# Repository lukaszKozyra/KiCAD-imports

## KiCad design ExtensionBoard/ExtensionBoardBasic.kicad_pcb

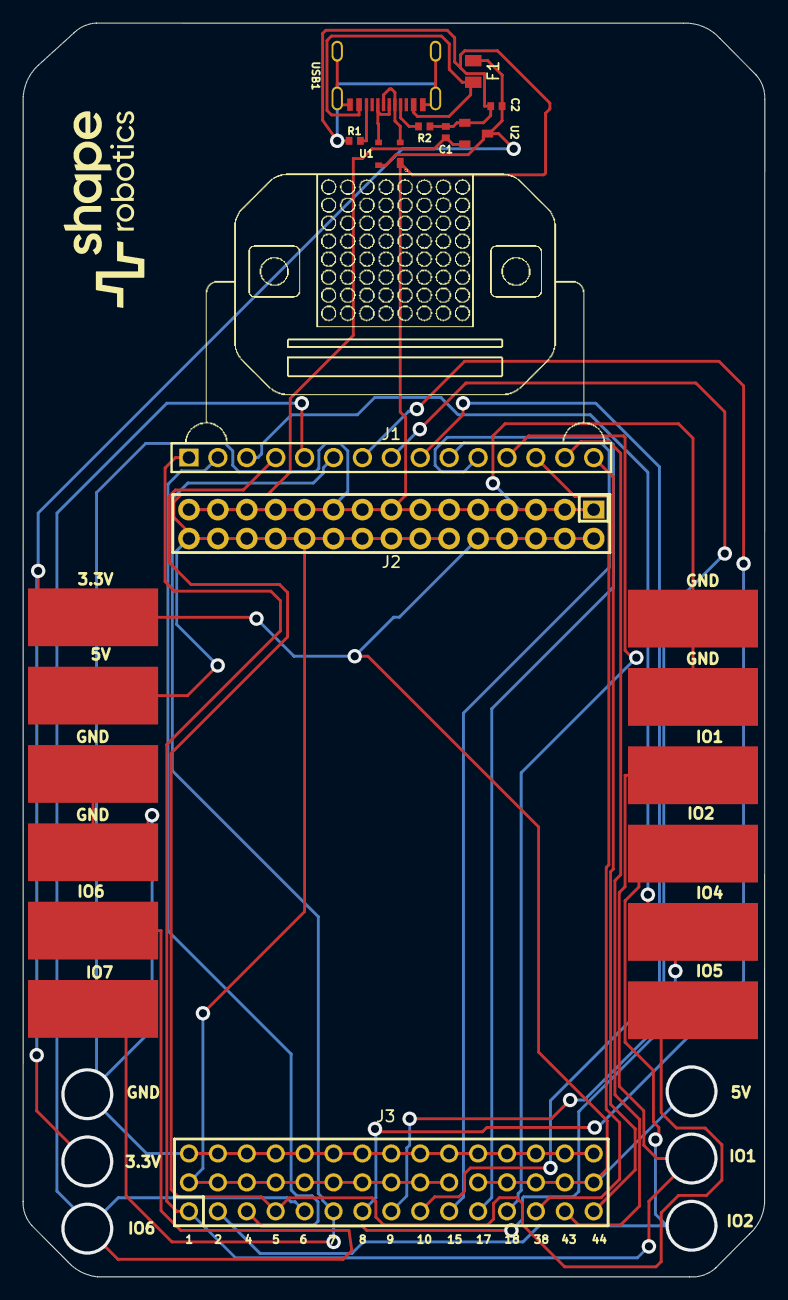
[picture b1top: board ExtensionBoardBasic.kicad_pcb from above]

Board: 4 copper layers, 65.2 x 110.2 mm, 11 parts (0 on the bottom side), 23 nets.

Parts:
C1, C2: 1uF; 0402C
F1: JSMD0805-110; 0805
J1: KH-2.54FH-1X15P-H8.5; HDR-TH_15P-P2.54-V-F
J2: PM2.54-2*15; HDR-TH_30P-P2.54-V-F-R2-C15-S2.54
J3: KH-2.54PH180-3X15P-L11.5; HDR-TH_15P-P2.54-V-M-R3-C15-S2.54
R1, R2: 5.1k; 0402R
U1: Unidirectional 5.5V 6V SOT-143 Diodes - ESD RoHS; SOT143B
U2: C193852; SOT-23
USB1: C167321

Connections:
+3.3: C1.2, J2.12, J2.14, J2.16, J2.18, J2.20, J2.22, J2.24, J2.26, J2.28, J2.30, J3.16, J3.17, J3.18, J3.19, J3.20, J3.21, J3.22, J3.23, J3.24, J3.25, U2.2 (VOUT)
+5: C2.2, F1.1, J2.2, J2.4, J2.6, J2.8, J2.10, J3.26, J3.27, J3.28, J3.29, J3.30, U1.4 (Vcc), U2.3 (VIN)
//IO01: J1.1, J3.1
//IO02: J1.2, J3.2
//IO4: J1.3, J3.3
//IO5: J1.4, J3.4
//IO6: J1.5, J3.5
//IO7: J1.6, J3.6
//IO8: J1.7, J3.7
//IO9: J1.8, J3.8
//IO10: J1.9, J3.9
//IO15: J1.10, J3.10
//IO17: J1.11, J3.11
//IO18: J1.12, J3.12
//IO38: J1.13, J3.13
//IO43: J1.14, J3.14
//IO44: J1.15, J3.15
//fuse: F1.2, USB1.A4B9 (VBUS), USB1.B4A9 (VBUS)
D_N: U1.2 (I/O_1), USB1.A7 (DN1), USB1.B7 (DN2)
D_P: U1.3 (I/O_2), USB1.A6 (DP1), USB1.B6 (DP2)
GND: C1.1, C2.1, J2.1, J2.3, J2.5, J2.7, J2.9, J2.11, J2.13, J2.15, J2.17, J2.19, J2.21, J2.23, J2.25, J2.27, J2.29, J3.31, J3.32, J3.33, J3.34, J3.35, J3.36, J3.37, J3.38, J3.39, J3.40, J3.41, J3.42, J3.43, J3.44, J3.45, R1.1, R2.1, U1.1 (GND), U2.1 (VSS), USB1.A1B12 (GND), USB1.B1A12 (GND)
unnamed: R2.2, USB1.A5 (CC1)
unnamed: R1.2, USB1.B5 (CC2)

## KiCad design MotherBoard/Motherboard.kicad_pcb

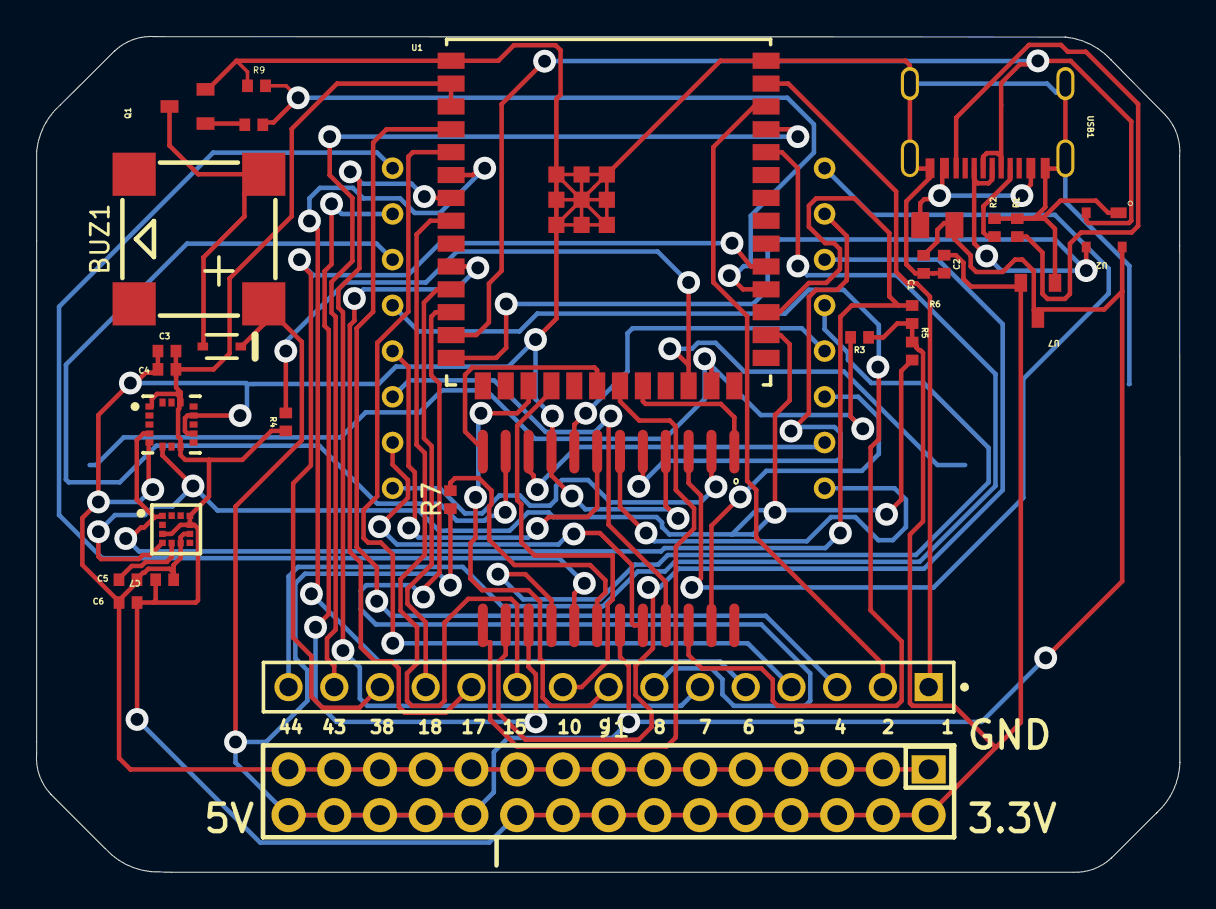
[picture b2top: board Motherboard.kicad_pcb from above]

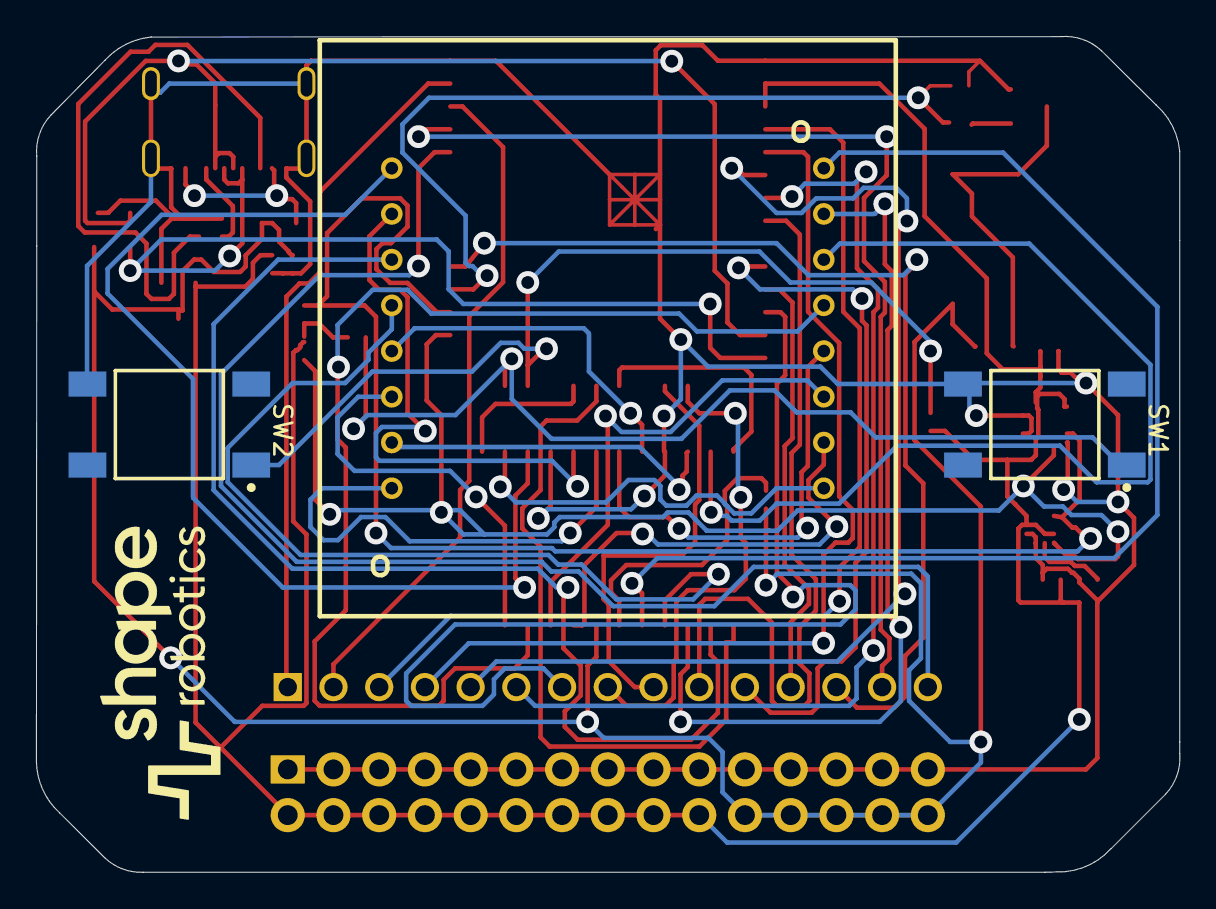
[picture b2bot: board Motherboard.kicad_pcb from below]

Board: 4 copper layers, 63.5 x 46.4 mm, 32 parts (3 on the bottom side), 51 nets.

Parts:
BUZ1: 2.7kHz; BUZ-SMD_4P-L8.5-W8.5-P8.50-BR
C1, C2: 1uF; 0402C
C3: 10pF; 0402C
C4, C5, C6: 100nF; 0402C
C7: 10uF; 0402C
D1: 1N4148WS-7-F; DIOD-SOD323-2-A_V
F1: JSMD0805-110; 0805
J1: 22-28-4157; FP-22-28-4157-MFG
J2: X6521WV-2x15H-C60D30; HDR-TH_30P-P2.54-V-F-R2-C15-S2.54
L1: SZ421288N/64; LED-SEG-TH_SZ421288N-64
Q1: NCE2302; SOT-23
R1, R2: 5.1k; 0402R
R3, R4, R5, R6, R7, R9: 10K; 0402R
R8: 470; 0402R
SW1, SW2: FSM4JSMATR; TECO-FSM4JSMATR_V
U1: ESP32 S3; ESP32 S3 WROOM 1
U2: Unidirectional 5.5V 6V SOT-143 Diodes - ESD RoHS; SOT143B
U4: LIS2MDLTR; FP-LGA-12-DM00170568-MFG
U5: LIS3DHTR; FP-LGA-16-7983231-MFG
U6: MAX7219M/TR; SOP-24_L15.4-W7.5-P1.27-LS10.4-BL
U7: C193852; SOT-23
USB1: C167321

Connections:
+3.3: C2.2, C3.2, C4.1, C6.2, C7.2, J2.2, J2.4, J2.6, J2.8, J2.10, J2.12, J2.14, J2.16, J2.18, J2.20, R3.2, R4.2, R5.1, R6.1, U1.2 (3V3), U1.3 (EN), U4.3 (CS), U4.9 (VDD), U4.10 (VDD_IO), U5.1 (Vdd_IO), U5.8 (CS), U5.14 (Vdd), U7.2 (VOUT)
+5: BUZ1.1 (+), C1.2, D1.2 (K), F1.1, J2.22, J2.24, J2.26, J2.28, J2.30, R7.1, U2.4 (Vcc), U6.19 (V+), U7.3 (VIN)
/B1: R3.1, SW1.1, U1.25 (IO48)
/B2: R4.1, SW2.1, U1.24 (IO47)
/BUZZER_SIG: R8.2, R9.2, U1.30 (IO37)
/DIG0: L1.9 (ROW1), U6.2 (DIG0)
/DIG1: L1.14 (ROW2), U6.11 (DIG1)
/DIG2: L1.8 (ROW3), U6.6 (DIG2)
/DIG3: L1.12 (ROW4), U6.7 (DIG3)
/DIG4: L1.1 (ROW5), U6.3 (DIG4)
/DIG5: L1.7 (ROW6), U6.10 (DIG5)
/DIG6: L1.2 (ROW7), U6.5 (DIG6)
/DIG7: L1.5 (ROW8), U6.8 (DIG7)
/IO01: J1.1, U1.39 (IO1)
/IO02: J1.2, U1.38 (IO2)
/IO4: J1.3, U1.4 (IO4)
/IO5: J1.4, U1.5 (IO5)
/IO6: J1.5, U1.6 (IO6)
/IO7: J1.6, U1.7 (IO7)
/IO8: J1.7, U1.12 (IO8)
/IO9: J1.8, U1.17 (IO9)
/IO10: J1.9, U1.18 (IO10)
/IO12: U1.20 (IO12), U6.12 (LOAD(CS#))
/IO13: U1.21 (IO13), U6.13 (CLK)
/IO14: U1.22 (IO14), U6.1 (DIN)
/IO15: J1.10, U1.8 (IO15)
/IO17: J1.11, U1.10 (IO17)
/IO18: J1.12, U1.11 (IO18)
/IO38: J1.13, U1.31 (IO38)
/IO43: J1.14, U1.37 (IO43)
/IO44: J1.15, U1.36 (IO44)
/SCL: R6.2, U1.29 (IO36), U4.1 (SCL/SPC), U5.4 (SCL/SPC)
/SDA: R5.2, U1.28 (IO35), U4.4 (SDA/SDI/SDO), U5.6 (SDA/SDI/SDO)
/SEGA: L1.3 (COL2), U6.14 (SEGA)
/SEGB: L1.4 (COL3), U6.16 (SEGB)
/SEGC: L1.10 (COL4), U6.20 (SEGC)
/SEGD: L1.6 (COL5), U6.23 (SEGD)
/SEGDP: L1.13 (COL1), U6.22 (SEGDP)
/SEGE: L1.11 (COL6), U6.21 (SEGE)
/SEGF: L1.15 (COL7), U6.15 (SEGF)
/SEGG: L1.16 (COL8), U6.17 (SEGG)
/fuse: F1.2, USB1.A4B9 (VBUS), USB1.B4A9 (VBUS)
D_N: U1.13 (IO19), U2.2 (I/O_1), USB1.A7 (DN1), USB1.B7 (DN2)
D_P: U1.14 (IO20), U2.3 (I/O_2), USB1.A6 (DP1), USB1.B6 (DP2)
GND: C1.1, C2.1, C3.1, C4.2, C5.2, C6.1, C7.1, J2.1, J2.3, J2.5, J2.7, J2.9, J2.11, J2.13, J2.15, J2.17, J2.19, J2.21, J2.23, J2.25, J2.27, J2.29, Q1.2 (S), R1.1, R2.1, R9.1, SW1.4, SW2.4, U1.1 (GND), U1.40 (GND), U1.41 (GND), U2.1 (GND), U4.6 (GND), U4.8 (GND), U5.5 (GND), U5.10 (RES), U5.12 (GND), U6.4 (GND), U6.9 (GND), U7.1 (VSS), USB1.A1B12 (GND), USB1.B1A12 (GND)
unnamed: BUZ1.2, D1.1 (A), Q1.3 (D)
unnamed: Q1.1 (G), R8.1
unnamed: C5.1, U4.5 (C1)
unnamed: R7.2, U6.18 (ISET)
unnamed: R2.2, USB1.A5 (CC1)
unnamed: R1.2, USB1.B5 (CC2)

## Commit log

2025-12-03 inital commit SPIN files v1
2025-12-03 spin update
2025-12-04 motherboard imported and corrected
2025-12-04 extension board imported
